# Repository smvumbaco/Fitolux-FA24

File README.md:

MAKE SURE TO SUBMIT A PULL REQUEST BEFORE EACH BREAKING MERGE

# <PROJECT NAME>
<ADD BLURB ABOUT PROJECT>

## Directory Structure:
```
.
|
|───production  # contains files needed for final prototype
|   |
|   |───eCAD    # contains the KiCAD project
|   └───src     # contains the code needed for deployment
|
|───testing     # contains files relevant to testing components
|
└───README.md   # this file!
```

## Preferred Tools
- KiCAD for PCB development
- Visual Studio Code / PlatformIO for code development
- Git CLI / GitHub Desktop for managing Git

## Branches
> To isolate conflicts for schematics and code, we use two branches to actually develop off of depending on discipline
- `develop/ecad` is for schematic development, please create PR's into this branch for schematics and operate in this branch for layout
- `develop/src` is for code development, please create PR's into this branch for features

## References
- Schematics + Components (WIP)

## Practice Good Git Hygiene!
1. Only commit files you intended to change
2. Create branches for each feature, and larger branches for each development effort (i.e. ```develop/*```)
3. Check your branch before starting work
4. Pull frequently to avoid conflicts
5. Make Pull Requests when you are ready to merge into a larger branch

## Git Resources

* [Setting up Git](https://fanatical-colossus-434.notion.site/Git-Installation-and-Setup-d07b7d1ab5544424876f9fd3b4a0b312)
* [Intro to Git Crash Course](https://fanatical-colossus-434.notion.site/Crash-Course-Intro-to-Git-809641611da9478b8f9cca8fd97e49fe)

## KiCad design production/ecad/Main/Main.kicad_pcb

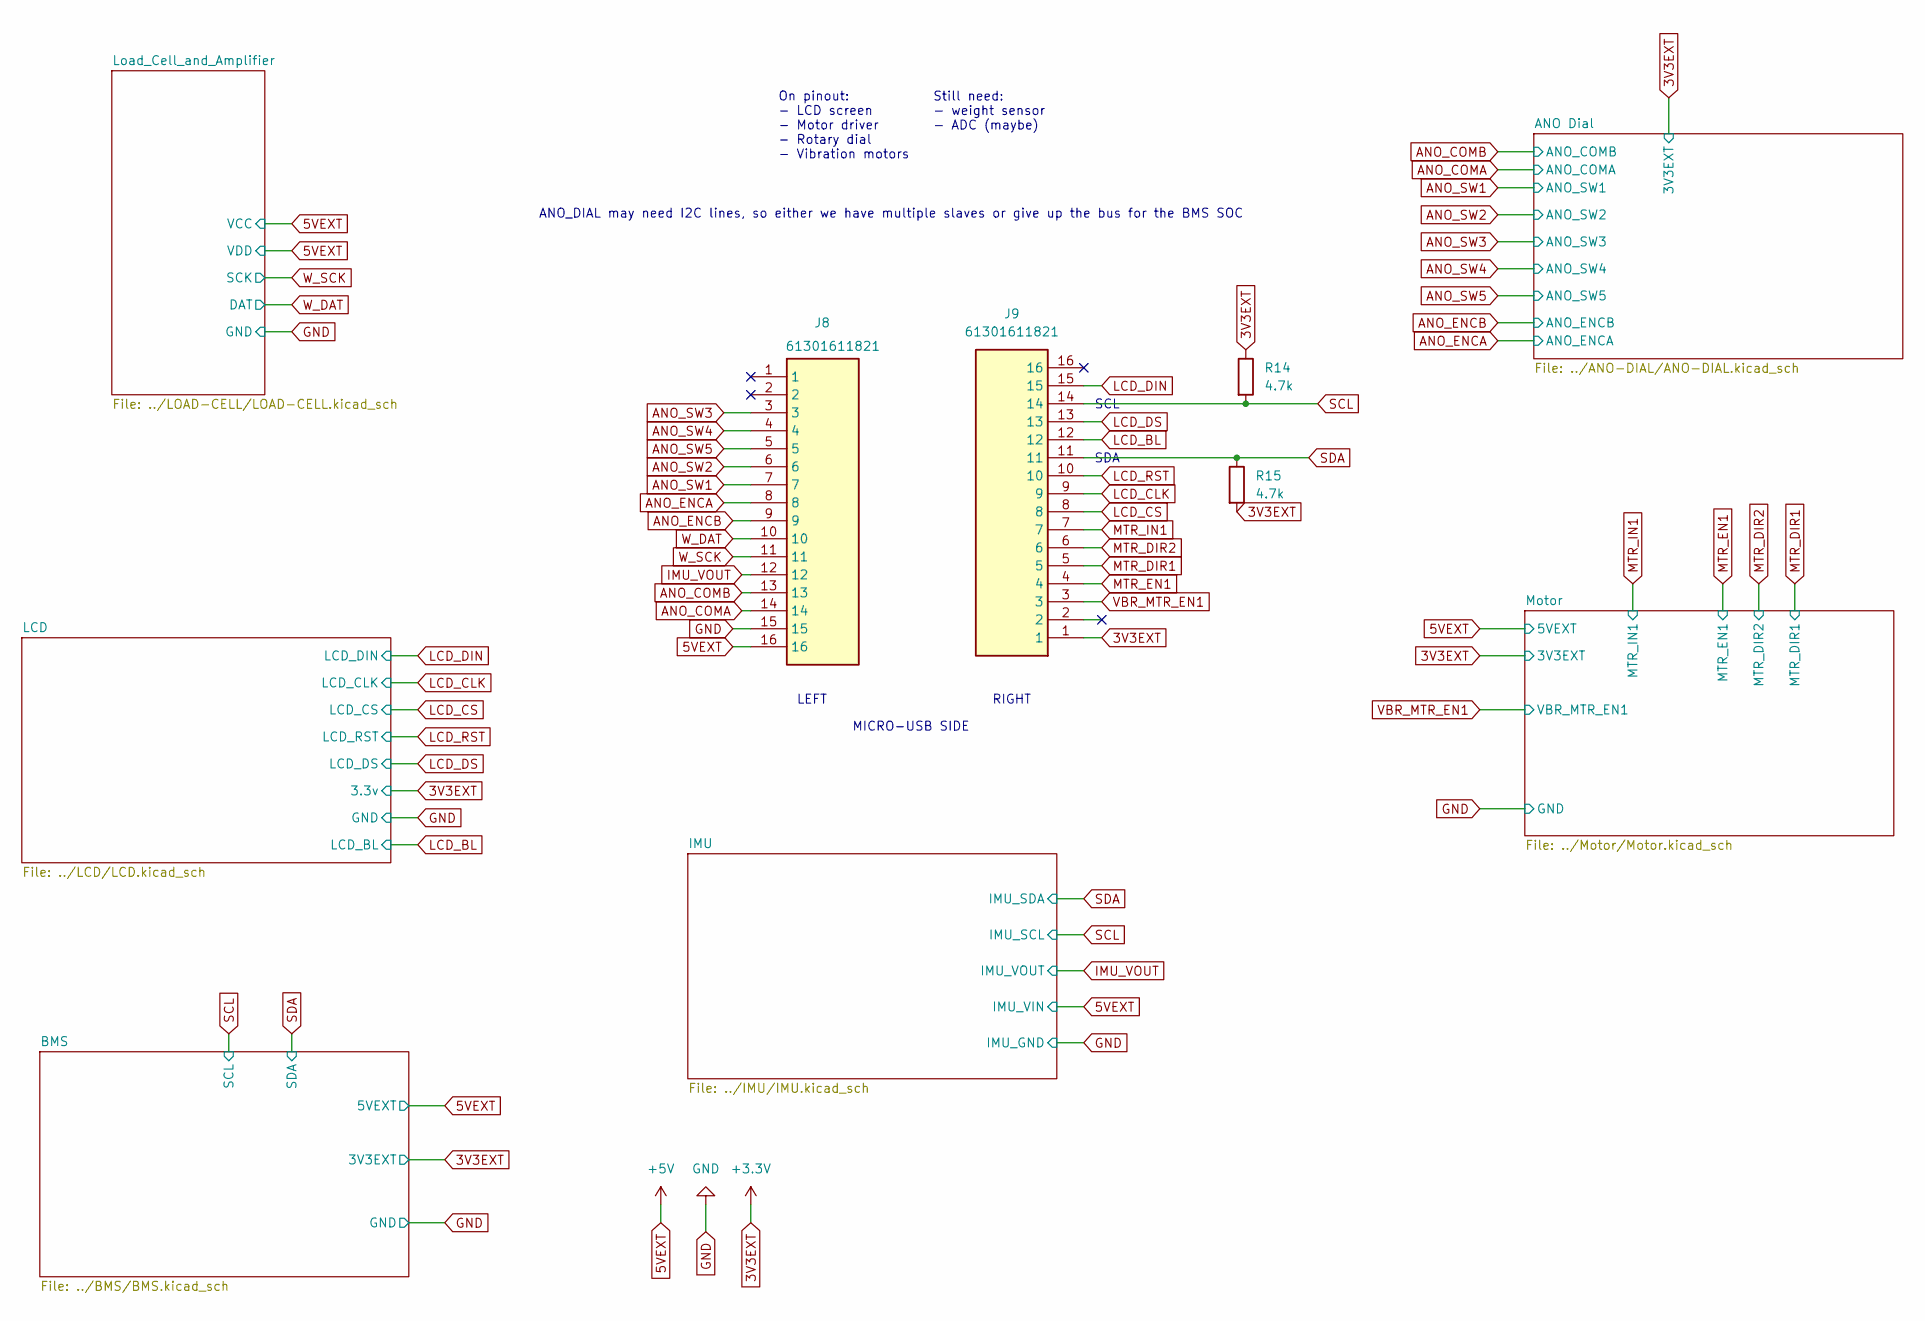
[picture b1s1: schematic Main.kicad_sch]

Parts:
J8, J9: 61301611821; 15posheader; Manufacturer_Part_Number 61301611821; Mouser Part Number 710-61301611821
R14, R15: 4.7k; R_0603_1608Metric_Pad0.98x0.95mm_HandSolder

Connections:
3V3EXT: J9.1, R14.1, R15.2; also elsewhere on the board
5VEXT: J8.16; also elsewhere on the board
ANO_COMA: J8.14; also elsewhere on the board
ANO_COMB: J8.13
ANO_ENCA: J8.8; also elsewhere on the board
ANO_ENCB: J8.9; also elsewhere on the board
ANO_SW1: J8.7; also elsewhere on the board
ANO_SW2: J8.6; also elsewhere on the board
ANO_SW3: J8.3; also elsewhere on the board
ANO_SW4: J8.4; also elsewhere on the board
ANO_SW5: J8.5; also elsewhere on the board
GND: J8.15; also elsewhere on the board
IMU_VOUT: J8.12; also elsewhere on the board
LCD_BL: J9.12; also elsewhere on the board
LCD_CLK: J9.9; also elsewhere on the board
LCD_CS: J9.8; also elsewhere on the board
LCD_DIN: J9.15; also elsewhere on the board
LCD_DS: J9.13; also elsewhere on the board
LCD_RST: J9.10; also elsewhere on the board
MTR_DIR1: J9.5; also elsewhere on the board
MTR_DIR2: J9.6; also elsewhere on the board
MTR_EN1: J9.4; also elsewhere on the board
MTR_IN1: J9.7; also elsewhere on the board
SCL: J9.14, R14.2; also elsewhere on the board
SDA: J9.11, R15.1; also elsewhere on the board
VBR_MTR_EN1: J9.3; also elsewhere on the board
W_DAT: J8.10; also elsewhere on the board
W_SCK: J8.11; also elsewhere on the board

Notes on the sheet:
LEFT
Still need: - weight sensor - ADC (maybe)
SDA
MICRO-USB SIDE
RIGHT
ANO_DIAL may need I2C lines, so either we have multiple slaves or give up the bus for the BMS SOC
SCL
On pinout: - LCD screen - Motor driver - Rotary dial - Vibration motors

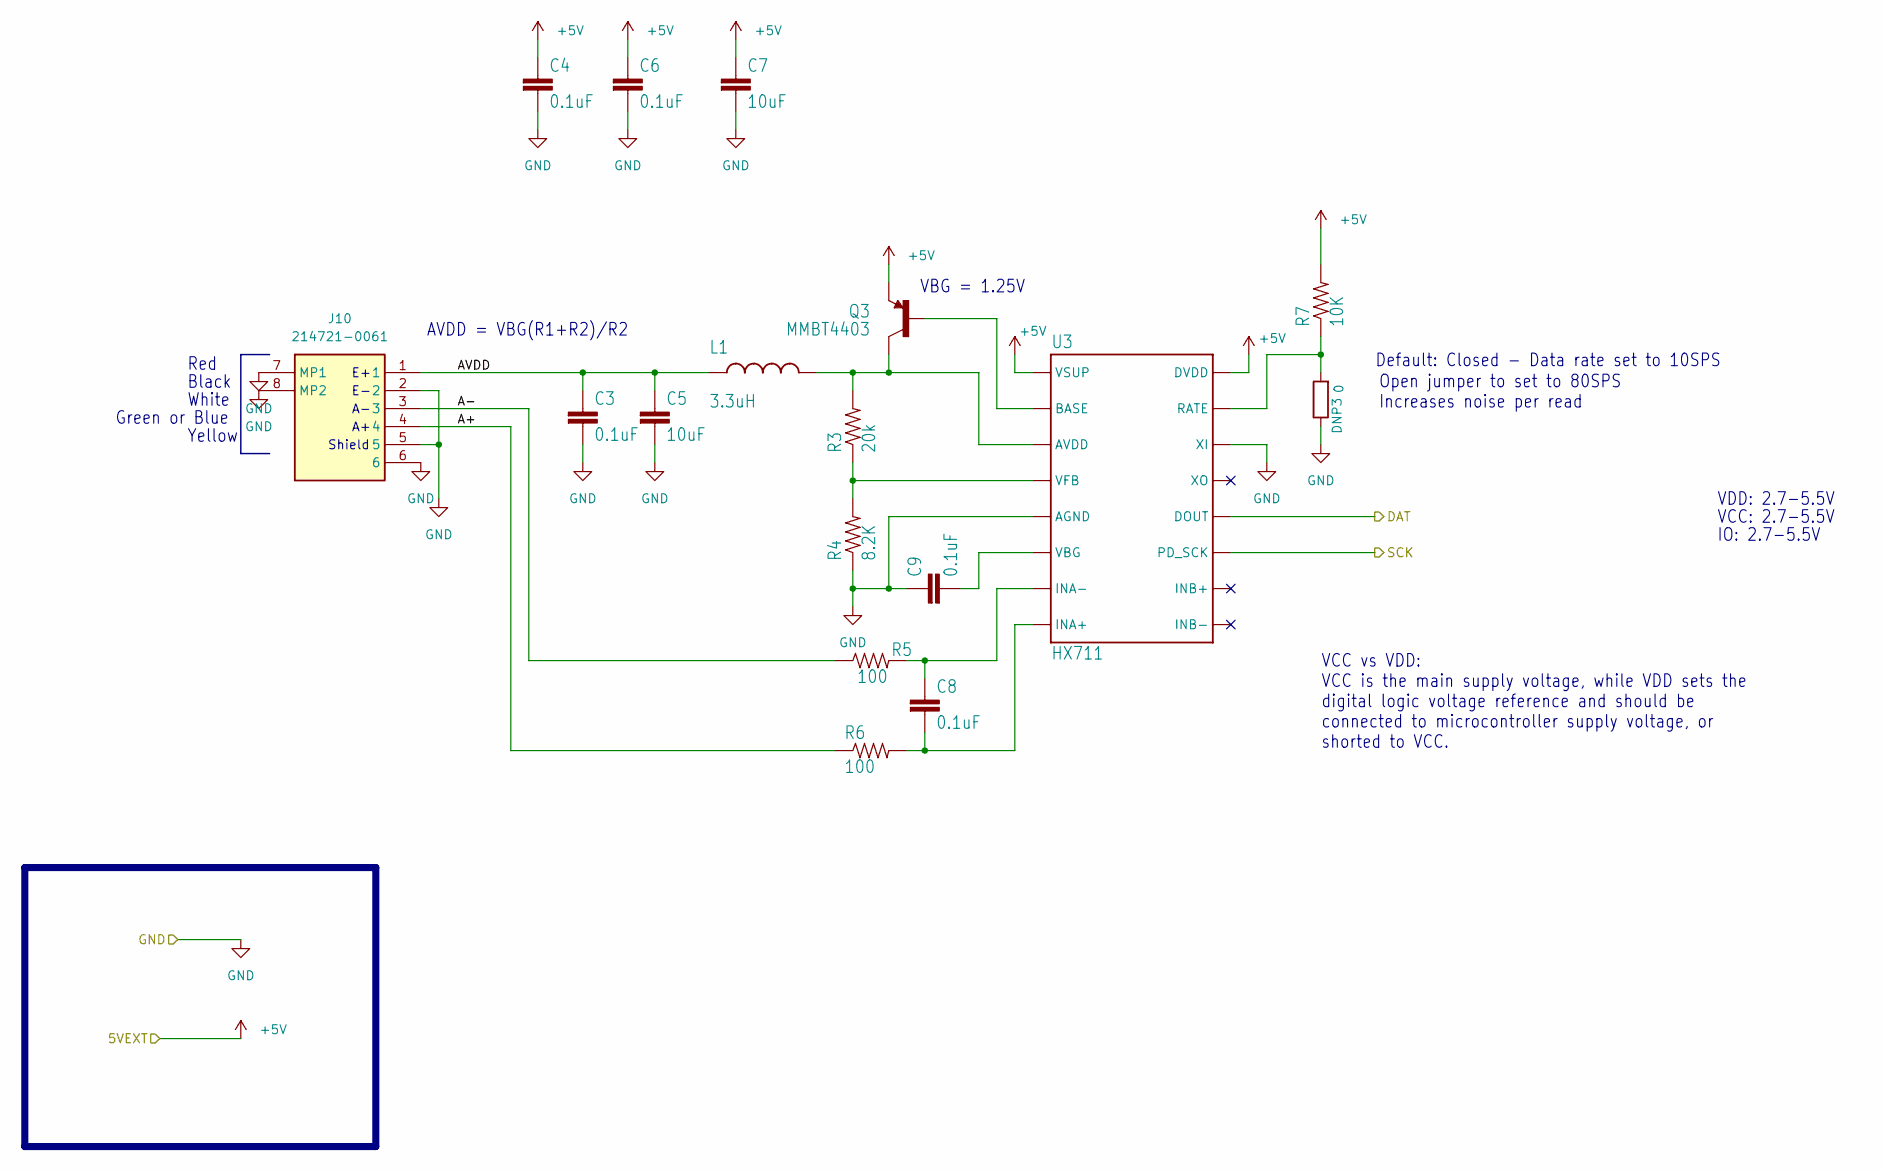
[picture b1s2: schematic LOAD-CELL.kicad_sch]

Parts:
C3, C4, C6, C8, C9: 0.1uF; C_0603_1608Metric
C5, C7: 10uF; C_0603_1608Metric
DNP3: 0; R_0603_1608Metric
J10: 214721-0061; 6_pos_connector; Manufacturer_Part_Number 214721-0061
L1: 3.3uH; L_0805_2012Metric
Q3: MMBT4403; mmbt4403
R3: 20k
R4: 8.2K; 8p2k
R5, R6: 100; 100ohm
R7: 10K; 10k
U3: HX711

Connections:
5VEXT: C4.1, C6.1, C7.1, Q3.2 (E), R7.2, U3.1 (VSUP), U3.16 (DVDD); also elsewhere on the board
/Load_Cell_and_Amplifier/A+: J10.4, R6.1
/Load_Cell_and_Amplifier/A-: J10.3, R5.1
/Load_Cell_and_Amplifier/AVDD: C3.1, C5.1, J10.1, L1.1
GND: C3.2, C4.2, C5.2, C6.2, C7.2, C9.1, DNP3.1, J10.2, J10.5, J10.6, J10.7 (MP1), J10.8 (MP2), R4.1, U3.5 (AGND), U3.14 (XI); also elsewhere on the board
unnamed: Q3.1 (B), U3.2 (BASE)
unnamed: L1.2, Q3.3 (C), R3.2, U3.3 (AVDD)
unnamed: C8.2, R6.2, U3.8 (INA+)
unnamed: C8.1, R5.2, U3.7 (INA-)
unnamed: DNP3.2, R7.1, U3.15 (RATE)
unnamed: C9.2, U3.6 (VBG)
unnamed: R3.1, R4.2, U3.4 (VFB)
W_DAT: U3.12 (DOUT); also elsewhere on the board
W_SCK: U3.11 (PD_SCK); also elsewhere on the board

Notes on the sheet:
Green or Blue
Shield
VCC vs VDD: VCC is the main supply voltage, while VDD sets the digital logic voltage reference and should be connected to microcontroller supply voltage, or shorted to VCC.
Open jumper to set to 80SPS Increases noise per read
Yellow
VDD: 2.7-5.5V
Red
VCC: 2.7-5.5V
Default: Closed - Data rate set to 10SPS
Black
AVDD = VBG(R1+R2)/R2
IO: 2.7-5.5V
White
VBG = 1.25V

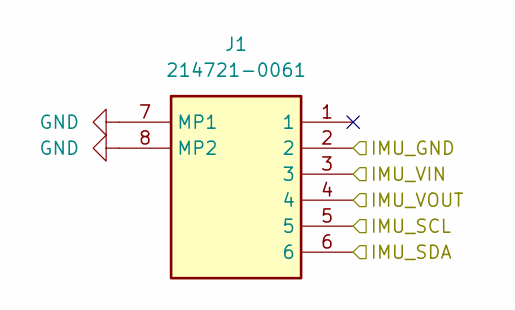
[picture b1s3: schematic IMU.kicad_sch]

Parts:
J1: 214721-0061; 6_pos_connector; Manufacturer_Part_Number 214721-0061

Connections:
5VEXT: J1.3; also elsewhere on the board
GND: J1.2, J1.7 (MP1), J1.8 (MP2); also elsewhere on the board
IMU_VOUT: J1.4; also elsewhere on the board
SCL: J1.5; also elsewhere on the board
SDA: J1.6; also elsewhere on the board

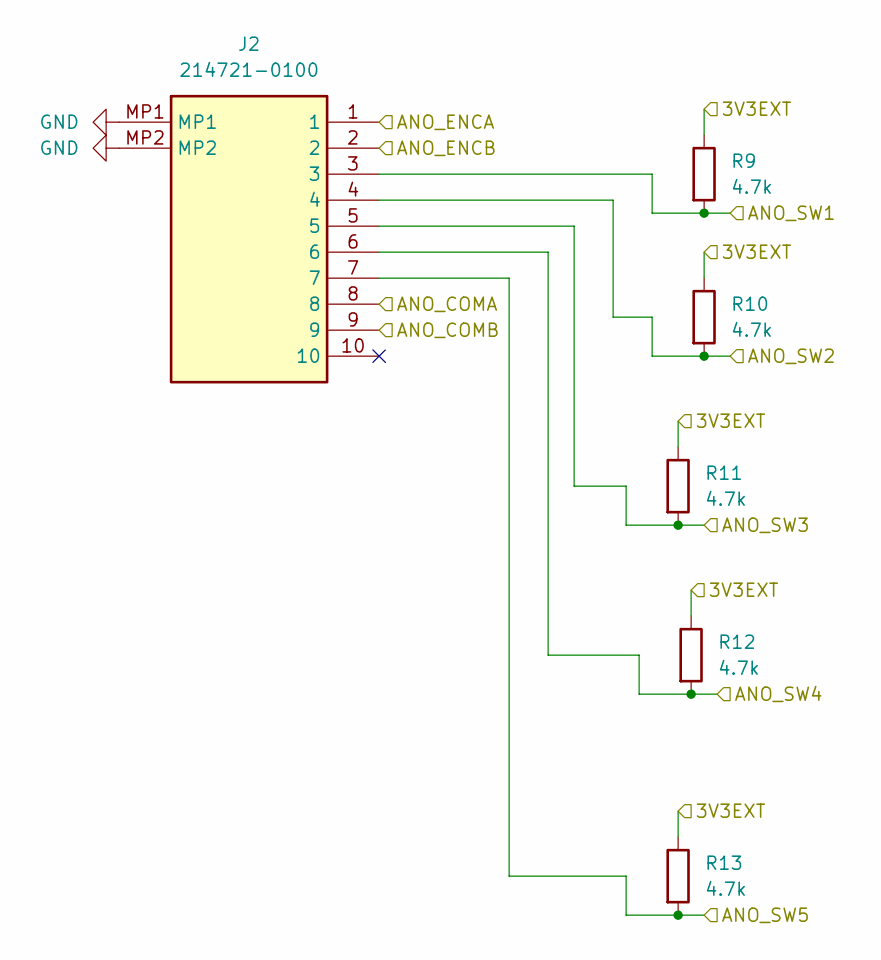
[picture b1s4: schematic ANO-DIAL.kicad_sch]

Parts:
J2: 214721-0100; 8positionheader; Mouser Part Number 538-214721-0100
R9, R10, R11, R12, R13: 4.7k; R_0603_1608Metric

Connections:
3V3EXT: R9.1, R10.1, R11.1, R12.1, R13.1; also elsewhere on the board
ANO_COMA: J2.8; also elsewhere on the board
ANO_ENCA: J2.1; also elsewhere on the board
ANO_ENCB: J2.2; also elsewhere on the board
ANO_SW1: J2.3, R9.2; also elsewhere on the board
ANO_SW2: J2.4, R10.2; also elsewhere on the board
ANO_SW3: J2.5, R11.2; also elsewhere on the board
ANO_SW4: J2.6, R12.2; also elsewhere on the board
ANO_SW5: J2.7, R13.2; also elsewhere on the board
GND: J2.MP1, J2.MP2; also elsewhere on the board

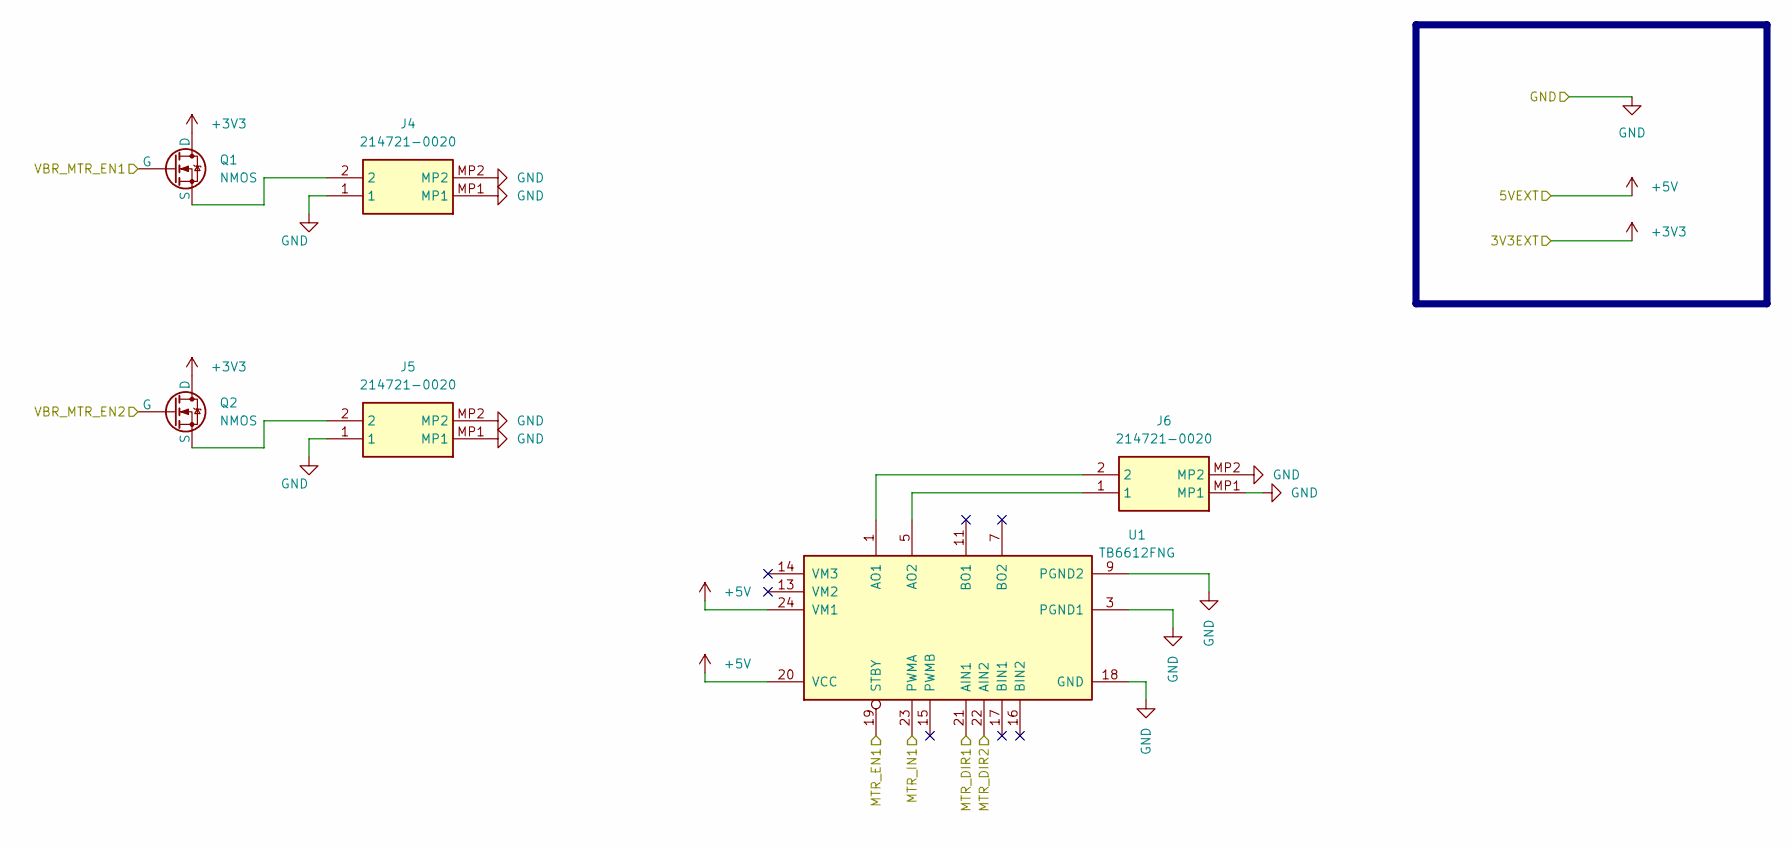
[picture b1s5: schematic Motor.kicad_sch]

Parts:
J4, J5, J6: 214721-0020; 2positionheader; Mouser Part Number 538-214721-0020
Q1, Q2: NMOS; SOT50P160X90-3N
U1: TB6612FNG; SSOP-24_5.3x8.2mm_P0.65mm

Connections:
3V3EXT: Q1.1 (D), Q2.1 (D); also elsewhere on the board
5VEXT: U1.20 (VCC), U1.24 (VM1); also elsewhere on the board
GND: J4.1, J4.MP1, J4.MP2, J5.1, J5.MP1, J5.MP2, J6.MP1, J6.MP2, U1.3 (PGND1), U1.4 (PGND1), U1.9 (PGND2), U1.10 (PGND2), U1.18 (GND); also elsewhere on the board
MTR_DIR1: U1.21 (AIN1); also elsewhere on the board
MTR_DIR2: U1.22 (AIN2); also elsewhere on the board
MTR_EN1: U1.19 (STBY); also elsewhere on the board
MTR_IN1: U1.23 (PWMA); also elsewhere on the board
unnamed: J6.1, U1.5 (AO2), U1.6 (AO2)
unnamed: J6.2, U1.1 (AO1), U1.2 (AO1)
unnamed: J4.2, Q1.3 (S)
unnamed: J5.2, Q2.3 (S)
VBR_MTR_EN1: Q1.2 (G), Q2.2 (G); also elsewhere on the board

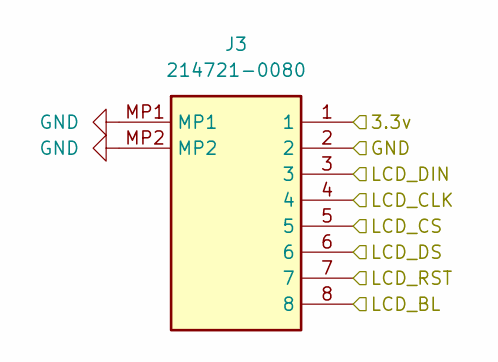
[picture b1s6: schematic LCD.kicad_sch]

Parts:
J3: 214721-0080; 8positionheader; Manufacturer_Part_Number 214721-0080

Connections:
3V3EXT: J3.1; also elsewhere on the board
GND: J3.2, J3.MP1, J3.MP2; also elsewhere on the board
LCD_BL: J3.8; also elsewhere on the board
LCD_CLK: J3.4; also elsewhere on the board
LCD_CS: J3.5; also elsewhere on the board
LCD_DIN: J3.3; also elsewhere on the board
LCD_DS: J3.6; also elsewhere on the board
LCD_RST: J3.7; also elsewhere on the board

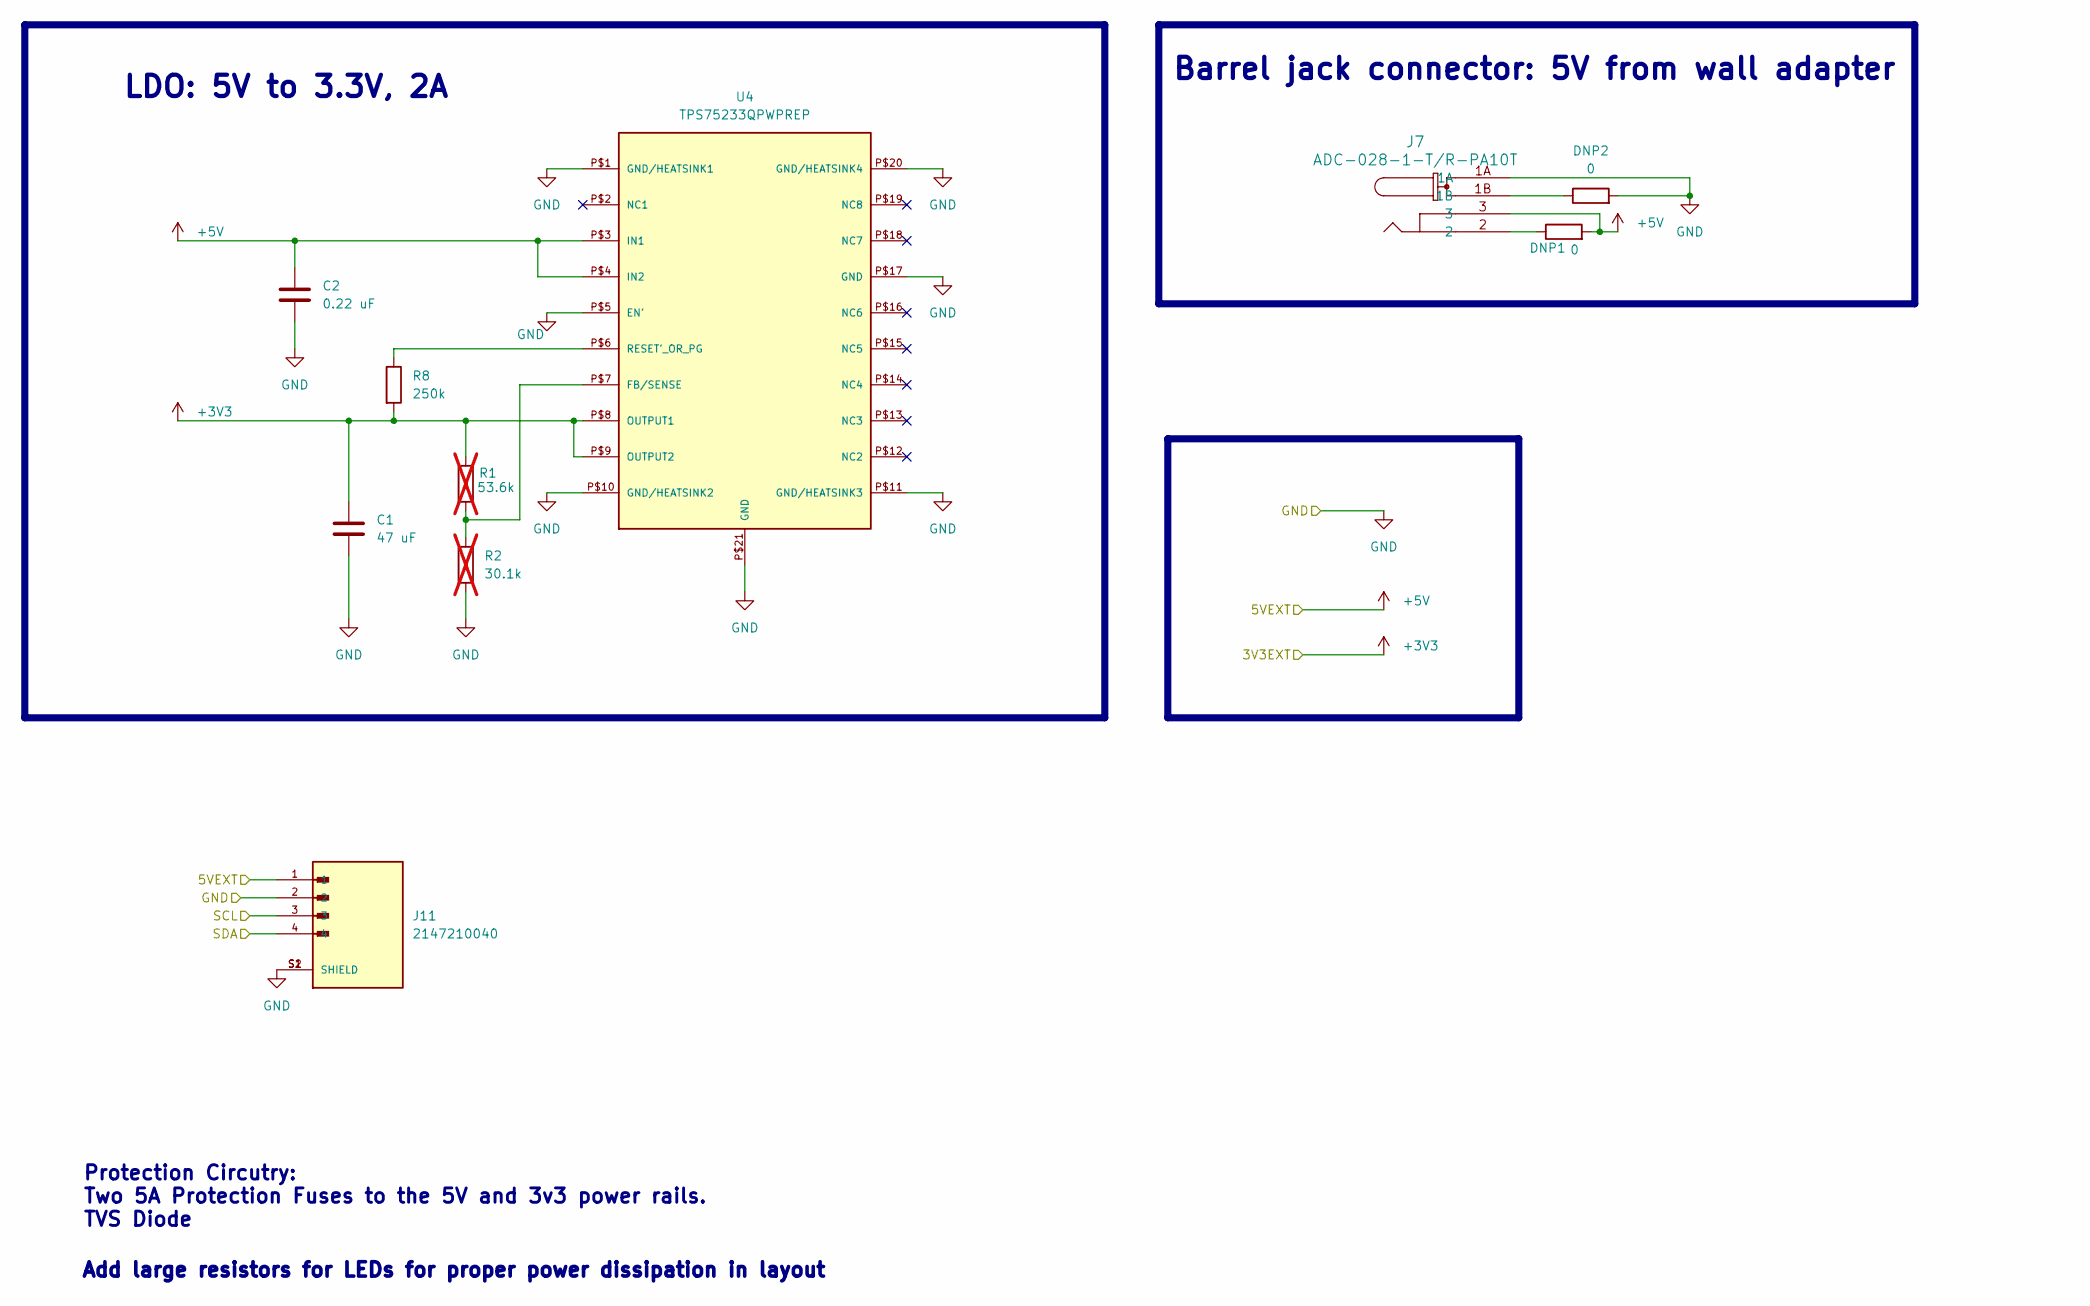
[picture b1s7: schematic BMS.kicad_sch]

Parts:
C1: 47 uF; C_0805_2012Metric
C2: 0.22 uF; C_0603_1608Metric
DNP1, DNP2: 0; R_0603_1608Metric
J7: ADC-028-1-T/R-PA10T; ADC-028-x-T&slash_R-PA10T_ADM
J11: 2147210040; 4positionheader; PARTREV A; DigiKey_Part_Number 900-2147210040CT-ND
R1: 53.6k; R_0603_1608Metric; not fitted
R2: 30.1k; R_0603_1608Metric; not fitted
R8: 250k; R_0603_1608Metric
U4: TPS75233QPWPREP

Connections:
3V3EXT: C1.1, R1.1, R8.2, U4.P$8 (OUTPUT1), U4.P$9 (OUTPUT2); also elsewhere on the board
5VEXT: C2.1, DNP1.2, J7.3, J11.1, U4.P$3 (IN1), U4.P$4 (IN2); also elsewhere on the board
GND: C1.2, C2.2, DNP2.2, J7.1A, J11.2, J11.S1 (SHIELD), J11.S2 (SHIELD), R2.2, U4.P$1 (GND/HEATSINK1), U4.P$5 (EN'), U4.P$10 (GND/HEATSINK2), U4.P$11 (GND/HEATSINK3), U4.P$17 (GND), U4.P$20 (GND/HEATSINK4), U4.P$21 (GND); also elsewhere on the board
unnamed: DNP1.1, J7.2
unnamed: DNP2.1, J7.1B
unnamed: R1.2, R2.1, U4.P$7 (FB/SENSE)
unnamed: R8.1, U4.P$6 (RESET'_OR_PG)
SCL: J11.3; also elsewhere on the board
SDA: J11.4; also elsewhere on the board

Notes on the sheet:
Barrel jack connector: 5V from wall adapter
LDO: 5V to 3.3V, 2A
Add large resistors for LEDs for proper power dissipation in layout
Protection Circutry: Two 5A Protection Fuses to the 5V and 3v3 power rails. TVS Diode

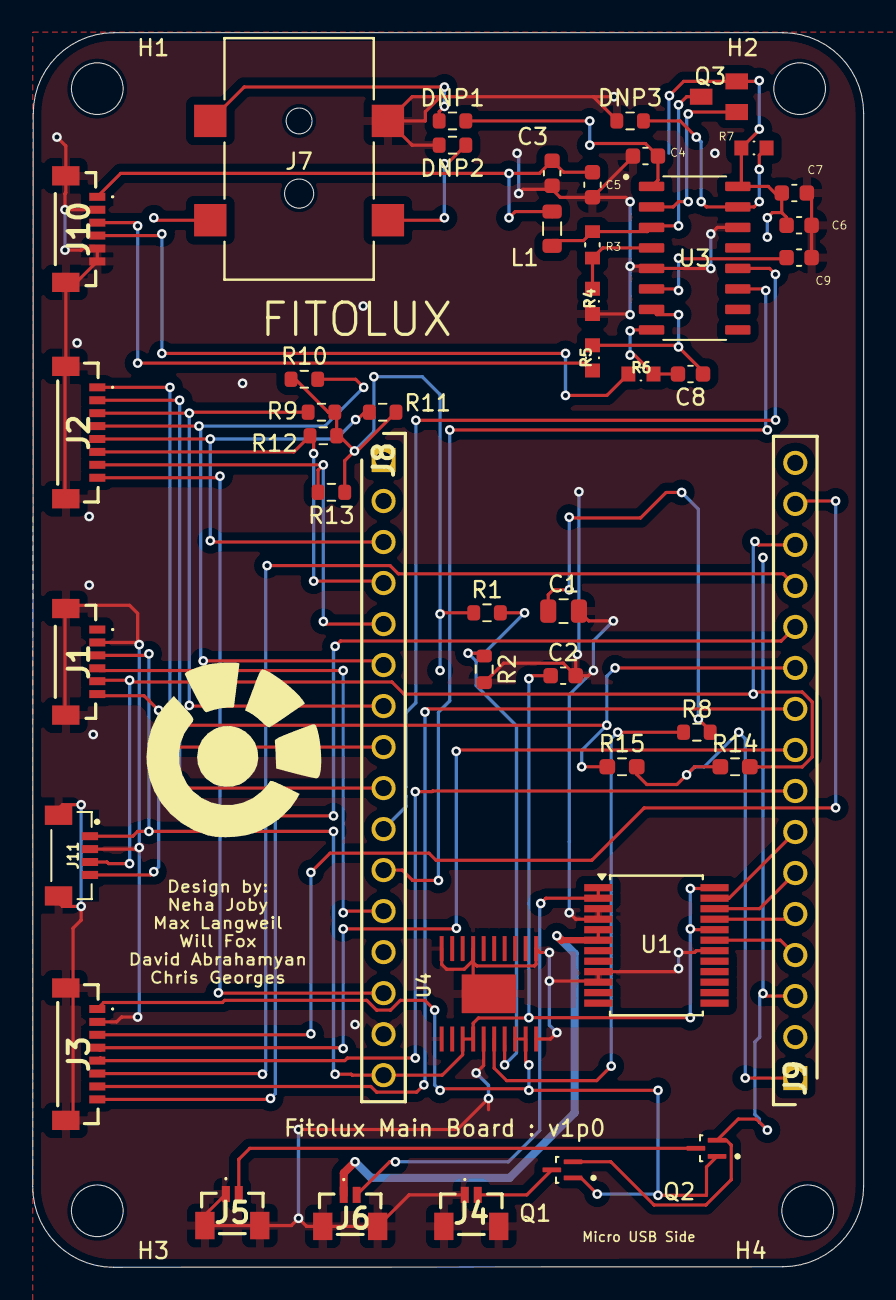
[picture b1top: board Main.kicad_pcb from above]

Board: 4 copper layers, 51.5 x 76.5 mm, 49 parts (0 on the bottom side), 45 nets.

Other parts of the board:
H1, H2, H3, H4: MountingHole; MountingHole_3.2mm_M3_ISO7380

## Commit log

2024-09-18 blank projects
2024-09-28 added header pins
2024-09-30 Created BMS schematic
2024-09-30 Create UI-Skeleton
2024-09-30 pinout first draft
2024-09-30 Update UI-Skeleton
    Updated with potential pin configuration
2024-09-30 added X's
2024-09-30 test creation of heirarchical sheets
2024-09-30 Added heirarchical sheets to main
2024-10-02 added hierchal labels and added libraries
2024-10-02 hierachel stuff
2024-10-07 added motor/LCD
2024-10-07 LDO schematic is complete
2024-10-07 main
2024-10-08 touches to schem
2024-10-08 updated schem
2024-10-09 schematic draft merged w neha
2024-10-14 feedback from Billayyy
2024-10-15 Working on BMS schem
2024-10-16 added load cell blck but did not wire it up yet
2024-10-16 connected to rabsperry pi
2024-10-16 LDO symbol added to components library
2024-10-17 Updated LDO schematic
2024-10-17 updated pullup resistors
2024-10-17 deleted B pins bc we won use them
2024-10-17 layout started
2024-10-17 Added new load cell connector, erased old thru hole connector from data side because we just have it on the pcb
2024-10-17 I think this stuff is trash but im just committing them before I delete them and I'll commit the delete too but keeping this here just in case I wanna bring it back
2024-10-17 Deleted obsolete Load Cell files
2024-10-17 erc check
2024-10-20 LDO schematic updated
2024-10-20 feedback
2024-10-20 Barrel jack added
2024-10-20 Barrel jack updated
2024-10-21 neha bms additions
2024-10-21 barreljack
2024-10-21 merged david and neha work
2024-10-21 Stylistic changes made
2024-10-24 Stylistic edits made
2024-10-24 more changes
2024-10-24 Added Weight Code
2024-10-24 changed pinout
2024-10-24 note
2024-10-27 reverted to Max branch from Wed and moved ANO button GPIO pins to input only
2024-10-27 BMS fixed
2024-10-28 Made some stylistic adjustments
2024-10-31 added imu and connector
2024-11-03 Added a MOD file to components folder
2024-11-03 Made a quick change on BMS
2024-11-03 added some footprints
2024-11-03 Added more footprints
2024-11-03 added connector for pisugar
2024-11-04 Moved MOD files into components > symbols folder
2024-11-04 DNP resistors were added
2024-11-04 Changed 53.6k resistor into two 27k resistors in series (BMS)
2024-11-04 merged with main
2024-11-04 All BMS footprints added to components folder
2024-11-04 All footprints for components + passives from BMS are assigned and ready for layout
2024-11-04 some changes
2024-11-04 merged neha's changes
2024-11-04 merged changes
2024-11-04 NMOS motor footprints added
2024-11-05 david changes
2024-11-05 my pushes
2024-11-05 connectors
2024-11-05 pushing platformio project
2024-11-05 Component placement complete
2024-11-05 GND, 5V, and 3v3 planes added
2024-11-05 did some routing
2024-11-05 more routing
2024-11-05 just some more routing
2024-11-05 my final changes
2024-11-05 1 last change
2024-11-06 schematic changes and pcb
2024-11-06 errors
2024-11-06 downsized board
2024-11-06 Routing updated
2024-11-06 Final changes updated
2024-11-07 Added 3V3, 5V, and GND power planes on layer 2
2024-11-07 Made updates from Sean
2024-11-07 i2c pull ups and changes
2024-11-07 mounting holes 3.2 mm
2024-11-07 added GND plane
2024-11-07 silkscreen labels adjusted
2024-11-07 more silkscreen updates
2024-11-07 silkscreen artwork
2024-11-07 final changes
2024-11-07 resistor and inductor
2024-11-07 footprints
2024-11-07 footprint
2024-11-08 error
2024-11-08 6 errors
2024-11-08 No more DRC errors yay!!
2024-11-08 some silk screen updates
2024-11-08 changed
2024-11-08 silkscreen changes
2024-11-08 changed fet footp
2024-11-09 moved connectors
2024-11-09 silkscreen
2024-11-18 added load cell and motor code
2024-12-02 i2c stuff and updates to anodial stuff
2024-12-03 pushing screen updates and state machine
2024-12-03 moved everything to main branch, got basic functionality and state machine functional
2024-12-04 updated screens
2024-12-05 Updates from past 2 nights
2024-12-05 cosmetic change'
